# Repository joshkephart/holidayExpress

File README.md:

# holidayExpress

Lego motor control using an esp32 and custom board.

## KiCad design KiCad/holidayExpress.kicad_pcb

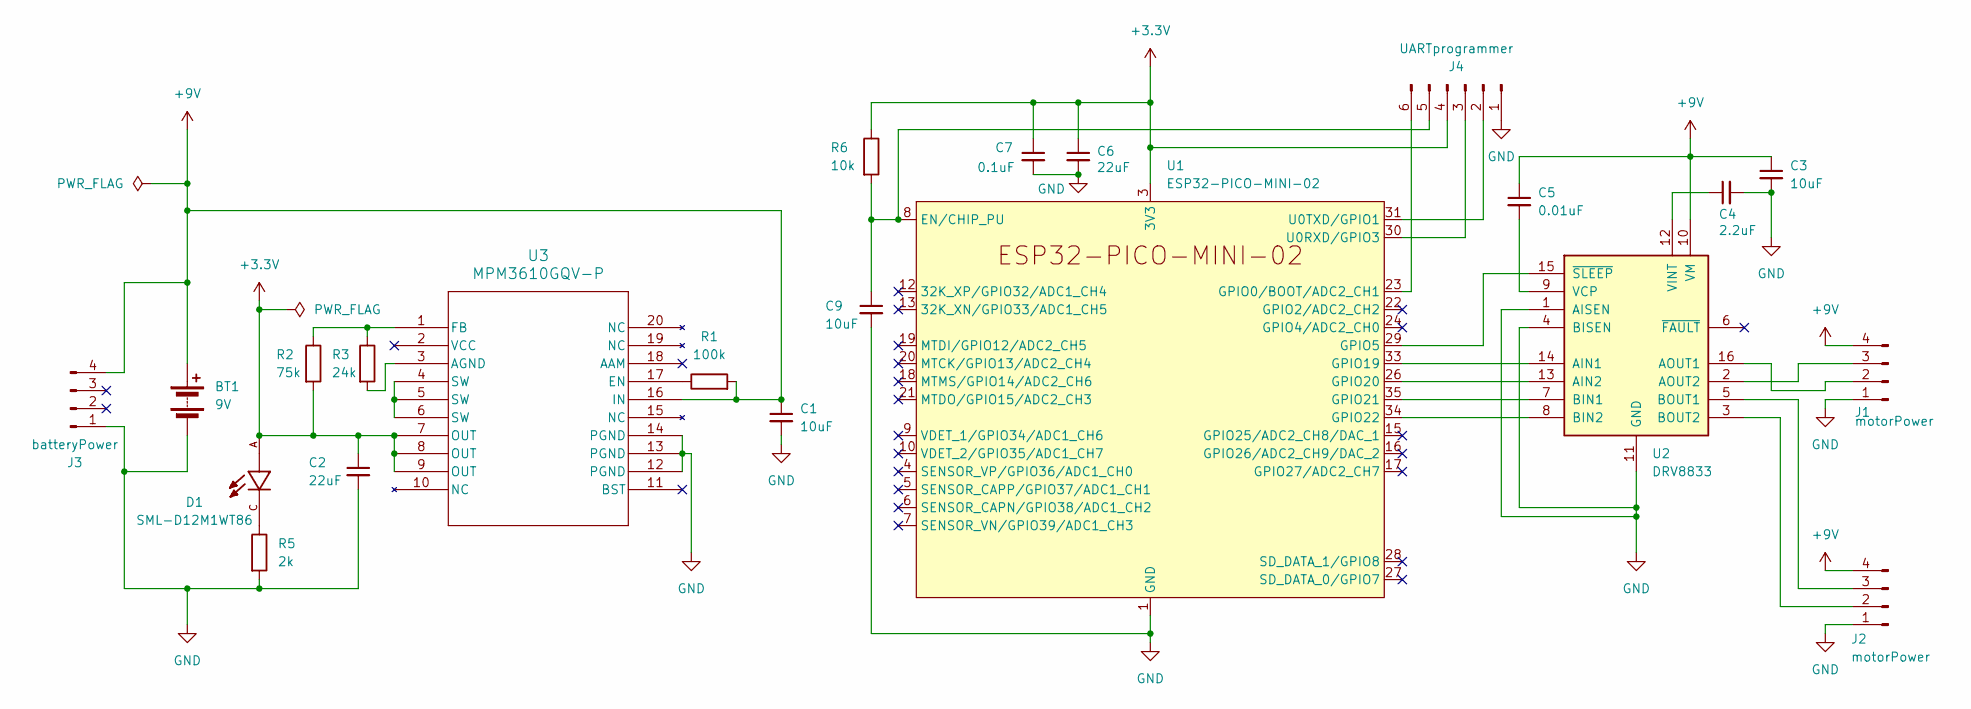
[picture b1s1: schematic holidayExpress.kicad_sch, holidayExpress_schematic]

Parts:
BT1: 9V
C1, C3, C9: 10uF; C_0402_1005Metric; LCSC Part # C7472949
C2, C6: 22uF; C_0402_1005Metric; LCSC Part # C3845593
C4: 2.2uF; C_0402_1005Metric; LCSC Part # C107369
C5: 0.01uF; C_0402_1005Metric; LCSC Part # C541371
C7: 0.1uF; C_0402_1005Metric; LCSC Part # C6955083
D1: SML-D12M1WT86; LED_SML-D12M1WT86; PARTREV 007; LCSC Part # C2922668
J1, J2: motorPower; PinHeader_1x04_P2.54mm_Vertical
J3: batteryPower; PinHeader_1x04_P2.54mm_Vertical
J4: UARTprogrammer; PinHeader_1x06_P2.54mm_Vertical
R1: 100k; R_0402_1005Metric; LCSC Part # C60491
R2: 75k; R_0402_1005Metric; LCSC Part # C137935
R3: 24k; R_0402_1005Metric; LCSC Part # C2933082
R5: 2k; R_0402_1005Metric; LCSC Part # C60488
R6: 10k; R_0402_1005Metric; LCSC Part # C60490
U1: ESP32-PICO-MINI-02; LCSC Part # C2980306
U2: DRV8833; Texas_RTY_WQFN-16-1EP_4x4mm_P0.65mm_EP2.1x2.1mm_ThermalVias; LCSC Part # C154936
U3: MPM3610GQV-P; QFN3p0x5p0x1p6_MPM3610_MNP; LCSC Part # C5183856

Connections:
+3.3V: C2.1, C6.1, C7.1, D1.A, J4.4, R2.2, R6.1, U1.3 (3V3), U3.7 (OUT), U3.8 (OUT), U3.9 (OUT)
+9V: BT1.1 (+), C1.1, C3.1, C5.1, J1.4, J2.4, J3.4, R1.2, U2.10 (VM), U3.16 (IN)
GND: BT1.2 (-), C1.2, C2.2, C3.2, C4.2, C6.2, C7.2, C9.2, J1.1, J2.1, J3.1, J4.1, R5.2, U1.1 (GND), U1.2 (GND), U1.11 (GND), U1.14 (GND), U1.36 (GND), U1.37 (GND), U1.38 (GND), U1.39 (GND), U1.40 (GND), U1.41 (GND), U1.42 (GND), U1.43 (GND), U1.44 (GND), U1.45 (GND), U1.46 (GND), U1.47 (GND), U1.48 (GND), U1.49 (GND), U1.50 (GND), U1.51 (GND), U1.52 (GND), U1.53 (GND), U2.1 (AISEN), U2.4 (BISEN), U2.11 (GND), U2.17 (GND), U3.12 (PGND), U3.13 (PGND), U3.14 (PGND)
unnamed: D1.C, R5.1
unnamed: J1.2, U2.16 (AOUT1)
unnamed: J1.3, U2.2 (AOUT2)
unnamed: J2.2, U2.3 (BOUT2)
unnamed: J2.3, U2.5 (BOUT1)
unnamed: J4.2, U1.31 (U0TXD/GPIO1)
unnamed: J4.3, U1.30 (U0RXD/GPIO3)
unnamed: C9.1, J4.5, R6.2, U1.8 (EN/CHIP_PU)
unnamed: J4.6, U1.23 (GPIO0/BOOT/ADC2_CH1)
unnamed: U1.29 (GPIO5), U2.15 (~SLEEP)
unnamed: U1.33 (GPIO19), U2.14 (AIN1)
unnamed: U1.26 (GPIO20), U2.13 (AIN2)
unnamed: U1.35 (GPIO21), U2.7 (BIN1)
unnamed: U1.34 (GPIO22), U2.8 (BIN2)
unnamed: C5.2, U2.9 (VCP)
unnamed: C4.1, U2.12 (VINT)
unnamed: R3.2, U3.3 (AGND)
unnamed: R1.1, U3.17 (EN)
unnamed: R2.1, R3.1, U3.1 (FB)
unnamed: U3.4 (SW), U3.5 (SW), U3.6 (SW)

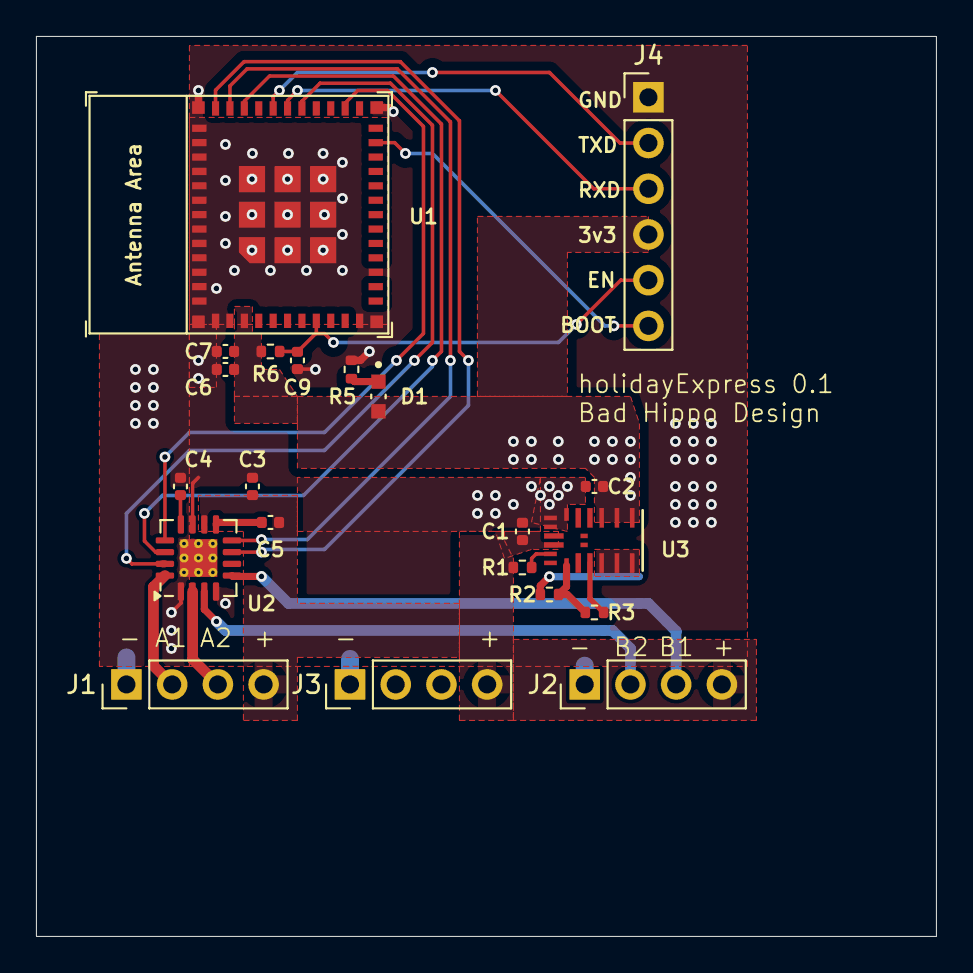
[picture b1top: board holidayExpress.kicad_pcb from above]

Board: 2 copper layers, 50.0 x 50.0 mm, 21 parts (0 on the bottom side), 23 nets.

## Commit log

2025-01-01 repo init
2025-02-17 initial circuit schematic
    Add initial implementation of KiCad circuit schematic for PCB.
2025-02-18 add boot and reset buttons
    Finish initial prototype schematic with reset and boot buttons for getting into flashing boot mode.
2025-02-22 add initial footprint selections
2025-03-01 add SDM LED and change to pin headers
    Add a power indicator LED. Change screw terminals to standard pin headers. Add project library for SMD LED symbol and footprint.
    Create initial PCB layout.
2025-03-06 complete initial PCB trace routing
2025-03-16 add ground plane and optimize routing
2025-03-16 adjust clearances and start DRC fixes
2025-03-16 add silkscreen labels and clear DRC errors
2025-03-20 add LCSC part numbers to symbols
2025-03-22 add .gitignore for PCB production files
    Ignore production files from various plugins.
    Add jlcpcb plugin project.db.
2025-03-22 fix path to production files in .gitignore
2025-04-06 begin moving to 0603 packages
2025-05-01 correct MPM3610 power input errors
    Connect MPM3610 In pin to power, make VCC unconnected. Re-orient UART programmer pins so that direct connection can be used with esp flashy tool. Reorient and optimize PCB layout around MPM changes, 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
2025-05-04 improve copper fill areas and routing
    Add copper fill zones with no thermal relief for SMD pads and use larger copper fills for 3.3V and 9V power planes.
2025-05-15 fix DRV8833 to use correct symbol
    Use QFN symbol so pin mapping matches footprint and part selection.
2025-07-27 final updates for prototype
    Minor cleanup for sending to JLCPCB for production of next prototype board revision
